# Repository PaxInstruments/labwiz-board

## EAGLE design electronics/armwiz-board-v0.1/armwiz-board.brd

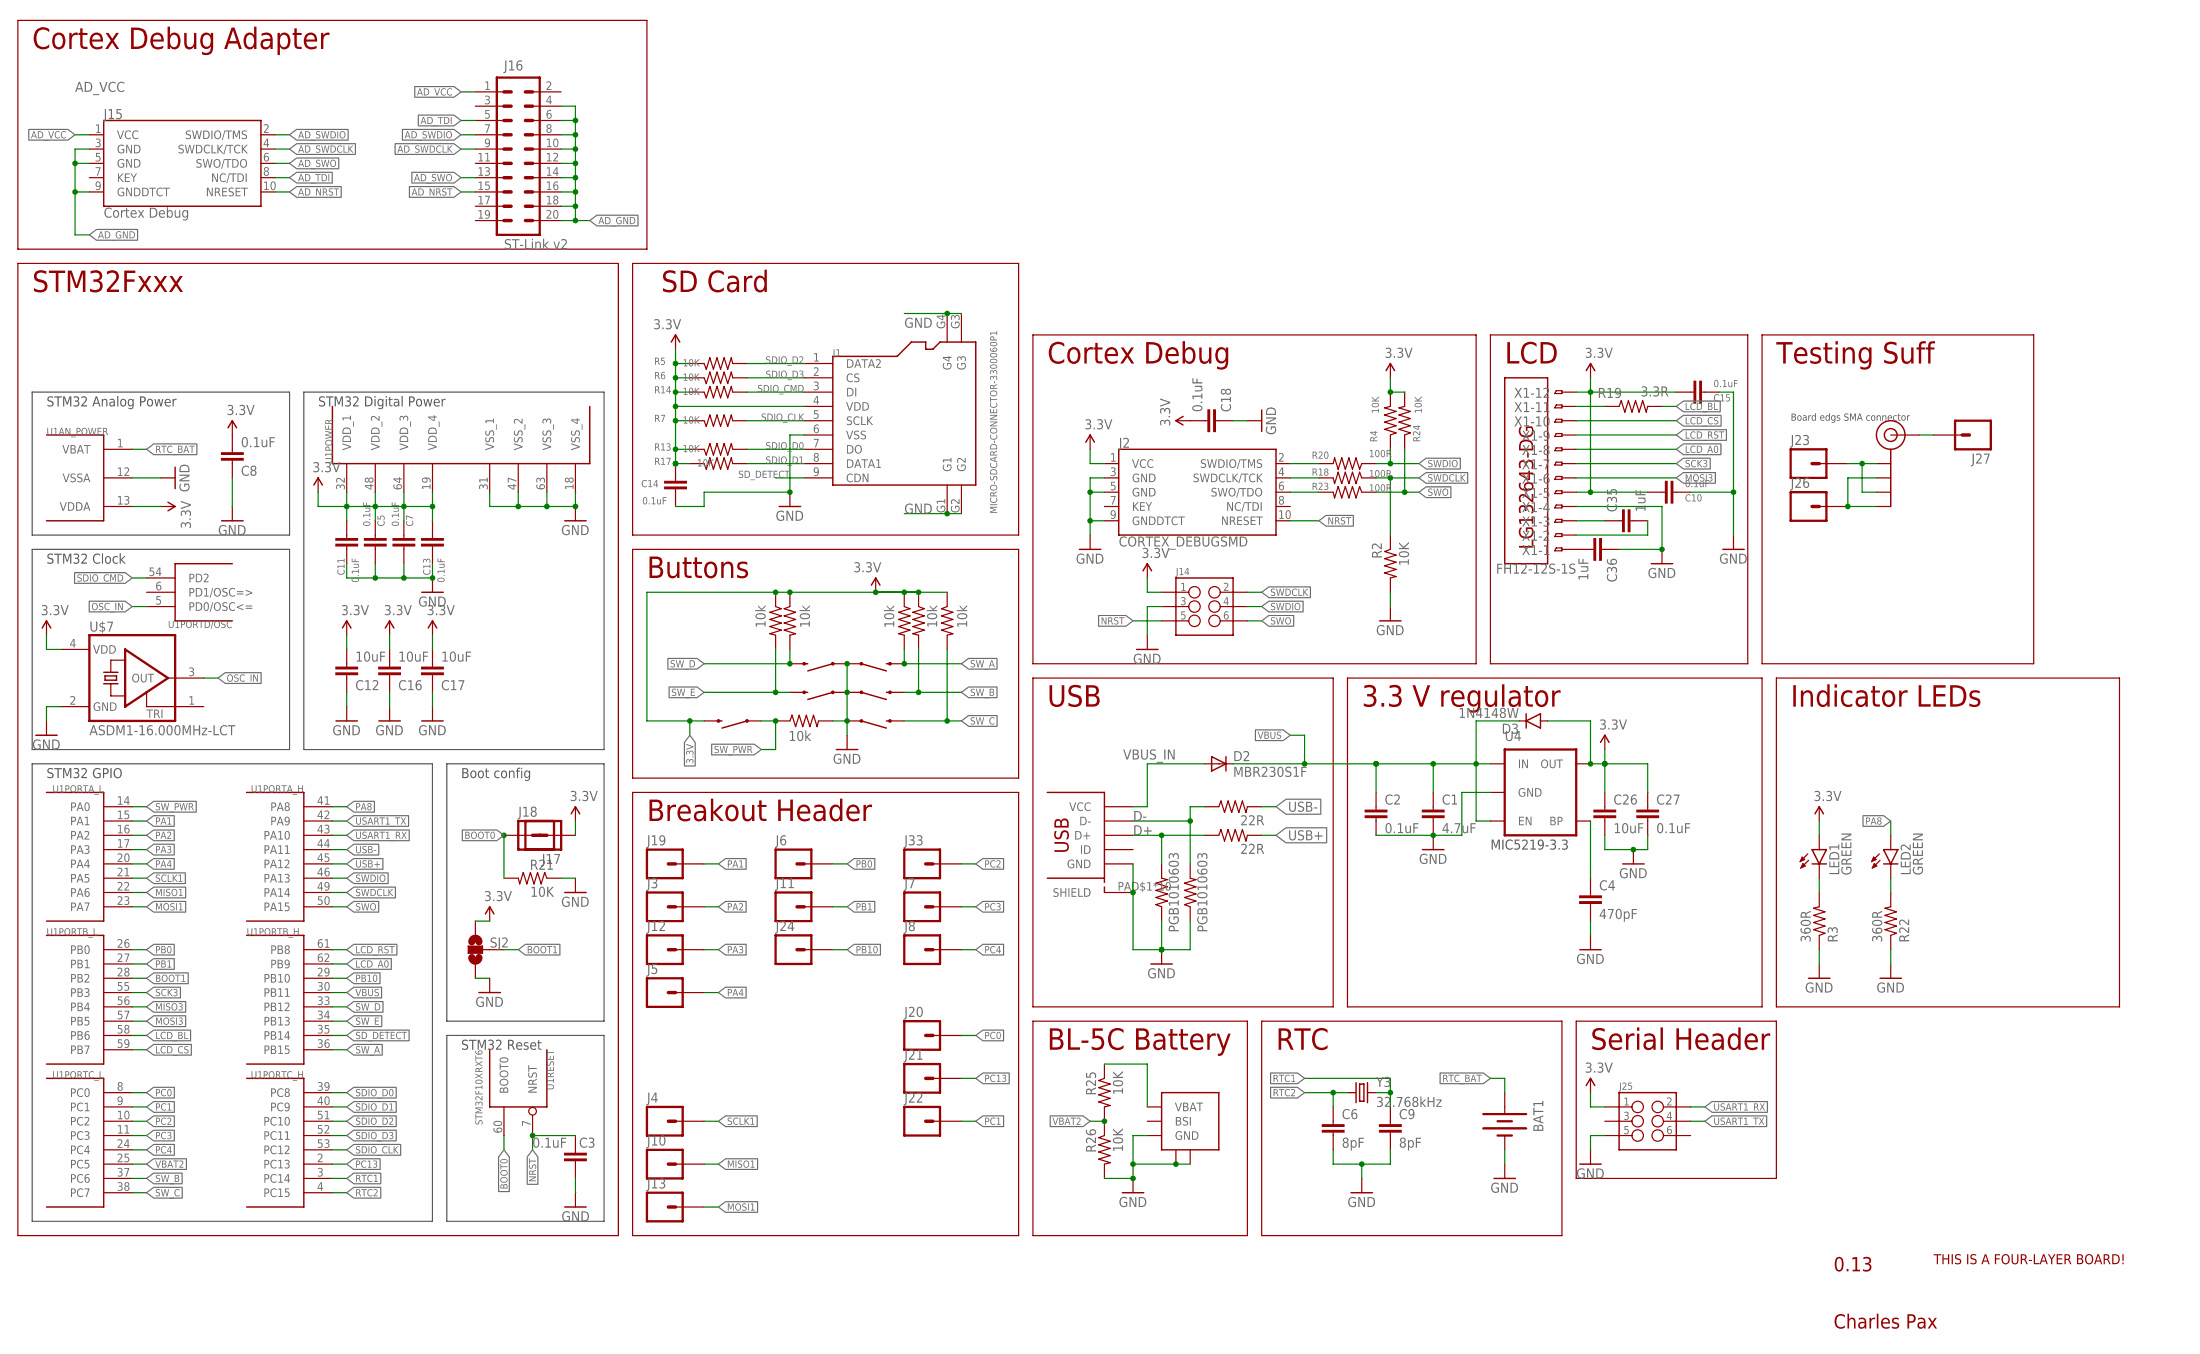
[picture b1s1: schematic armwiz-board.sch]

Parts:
BAT1: BATTERY12MM; BATTCON_12MM
C1: 4.7uF; C0402K
C2, C3, C5, C7, C8, C10, C11, C13, C14, C15, C18, C27: 0.1uF; C0402K
C4: 470pF; C0402K
C6, C9: 8pF; C0402K
C12, C16, C17, C26: 10uF; C0402K
C35, C36: 1uF; C0402K
D2: MBR230S1F; SOD123; MPN MBR230S1F-7
D3: 1N4148W; SOD-123
J1: MICRO-SDCARD-CONNECTOR-3300060P1; 9P-SMD-W-RING; MPN ST-TF-003A
J2: CORTEX_DEBUGSMD; SAMTECH_FTSH-105-01
J3, J4, J5, J6, J7, J8, J10, J11, J12, J13, J19, J20, J21, J22, J23, J24, J26, J27, J33: M01PTH; 1X01
J14, J25: M03X2PAX; CONNECTORS_2X3_SMT_POSTS_T400
J15: Cortex Debug; SAMTECH_FTSH-105-01
J16: ST-Link v2; 2X10
J17, J18: M01NOSILK-KIT; 1X01NS-KIT
J$1: SMA_EDGE; SMA-EDGE
LED1, LED2: GREEN; LED-0603
R1, R8, R11, R12, R15, R16: 10k; R0402
R2, R4, R5, R6, R7, R13, R14, R17, R21, R24, R25, R26: 10K; R0402
R3, R22: 360R; R0402
R9, R10: 22R; R0402
R18, R20, R23: 100R; R0402
R19: 3.3R; R0402
S1, S2, S3, S4, S5, S6: SWITCH-MOMENTARY-2SMD; TACTILE_SWITCH_SMD; MPN RS-187R05A2-DS MT RT
SJ2: SOLDERJUMPER_2WAYS; SJ_3
U1: STM32F10XRXT6; TQFP64
U4: MIC5219-3.3V; SOT23-5; MPN MIC5219-3.3YM5 TR
U$1: USB_MICROSMT+THRUHULE; USB_MICRO_THRUHOLE; MPN 10118194-0001LF
U$2: FOUR_LAYER_WARNING
U$3: BL-5C-CONNECTOR
U$5: LG132643-DG; MPN LG132643-DW
U$7: ASDM1-16.000MHz-LCT; ASE
X1: FH12-12S-1S; FH12-12S-1SH; MPN FH12-12S-1SH(55)
Y3: 32.768kHz; CRYSTAL-SMD-3.2X1.5MM
Z1, Z2: PGB1010603; SPARKFUN-RESISTORS_0603-RES; MPN PGB1010603NRHF

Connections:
3.3V: C5.1, C7.1, C8.2, C10.2, C11.2, C12.2, C13.2, C14.2, C15.2, C16.2, C17.2, C18.2, C26.1, C27.1, D3.A, J1.4 (VDD), J2.1 (VCC), J14.1, J18.1, J25.1, LED1.A, R4.2, R5.1, R6.1, R7.1, R8.1, R11.1, R12.1, R13.1, R14.1, R15.1, R16.1, R17.1, R24.2, S6.3 (2), SJ2.3, U1.13 (VDDA), U1.19 (VDD_4), U1.32 (VDD_1), U1.48 (VDD_2), U1.64 (VDD_3), U4.5 (OUT), U$7.4 (VDD), X1.5, X1.12
AD_GND: J15.3 (GND), J15.5 (GND), J15.9 (GNDDTCT), J16.4, J16.6, J16.8, J16.10, J16.12, J16.14, J16.16, J16.18, J16.20
AD_NRST: J15.10 (NRESET), J16.15
AD_SWDCLK: J15.4 (SWDCLK/TCK), J16.9
AD_SWDIO: J15.2 (SWDIO/TMS), J16.7
AD_SWO: J15.6 (SWO/TDO), J16.13
AD_TDI: J15.8 (NC/TDI), J16.5
AD_VCC: J15.1 (VCC), J16.1
BOOT0: J17.1, R21.2, U1.60 (BOOT0)
BOOT1: SJ2.2, U1.28 (PB2)
D+: R9.1, U$1.PIN$3 (D+), Z1.2
D-: R10.1, U$1.PIN$2 (D-), Z2.2
GND: BAT1.GND (-), C1.2, C2.2, C3.2, C4.2, C5.2, C6.2, C7.2, C8.1, C9.2, C10.1, C11.1, C12.1, C13.1, C14.1, C15.1, C16.1, C17.1, C18.1, C26.2, C27.2, C36.1, J1.6 (VSS), J1.G1, J1.G2, J1.G3, J1.G4, J2.3 (GND), J2.5 (GND), J2.9 (GNDDTCT), J14.3, J25.5, R1.2, R2.2, R3.1, R21.1, R22.1, R26.2, S1.1, S2.1, S3.1, S4.1, S5.1, SJ2.1, U1.12 (VSSA), U1.18 (VSS_4), U1.31 (VSS_1), U1.47 (VSS_2), U1.63 (VSS_3), U4.2 (GND), U$1.PAD$1 (SHIELD), U$1.PAD$2 (SHIELD), U$1.PAD$3 (SHIELD), U$1.PAD$4 (SHIELD), U$1.PAD$5 (SHIELD), U$1.PAD$6 (SHIELD), U$1.PAD$7 (SHIELD), U$1.PAD$8 (SHIELD), U$1.PAD$9 (SHIELD), U$1.PAD$10 (SHIELD), U$1.PIN$5 (GND), U$3.P$3 (GND), U$3.P$4, U$3.P$5, U$7.2 (GND), X1.4, Z1.1, Z2.1
LCD_A0: U1.62 (PB9), X1.8
LCD_BL: R19.2, U1.58 (PB6)
LCD_CS: U1.59 (PB7), X1.10
LCD_RST: U1.61 (PB8), X1.9
MISO1: J10.1, U1.22 (PA6)
MISO3: U1.56 (PB4)
MOSI1: J13.1, U1.23 (PA7)
MOSI3: U1.57 (PB5), X1.6
unnamed: C4.1, U4.4 (BP)
unnamed: R19.1, X1.11
unnamed: J2.4 (SWDCLK/TCK), R18.2
unnamed: LED1.C, R3.2
unnamed: LED2.C, R22.2
unnamed: J2.6 (SWO/TDO), R23.2
unnamed: J2.2 (SWDIO/TMS), R20.2
unnamed: J26.1, J$1.GND@1 (GND), J$1.GND@3 (GND)
unnamed: J23.1, J$1.GND@0 (GND), J$1.GND@2 (GND)
unnamed: R25.1, U$3.P$1 (VBAT)
unnamed: J27.1, J$1.SIG (SIGNAL)
unnamed: C35.1, X1.3
unnamed: C35.2, X1.2
unnamed: C36.2, X1.1
NRST: C3.1, J2.10 (NRESET), J14.5, U1.7 (NRST)
OSC_IN: U1.5 (PD0/OSC<=), U$7.3 (OUT)
PA1: J19.1, U1.15 (PA1)
PA2: J3.1, U1.16 (PA2)
PA3: J12.1, U1.17 (PA3)
PA4: J5.1, U1.20 (PA4)
PA8: LED2.A, U1.41 (PA8)
PB0: J6.1, U1.26 (PB0)
PB1: J11.1, U1.27 (PB1)
PB10: J24.1, U1.29 (PB10)
PC0: J20.1, U1.8 (PC0)
PC1: J22.1, U1.9 (PC1)
PC2: J33.1, U1.10 (PC2)
PC3: J7.1, U1.11 (PC3)
PC4: J8.1, U1.24 (PC4)
PC13: J21.1, U1.2 (PC13)
RTC1: C9.1, U1.3 (PC14), Y3.P$2 (2)
RTC2: C6.1, U1.4 (PC15), Y3.P$1 (1)
RTC_BAT: BAT1.PWR@1 (+), U1.1 (VBAT)
SCK3: U1.55 (PB3), X1.7
SCLK1: J4.1, U1.21 (PA5)
SDIO_CLK: J1.5 (SCLK), R7.2, U1.53 (PC12)
SDIO_CMD: J1.3 (DI), R14.2, U1.54 (PD2)
SDIO_D0: J1.7 (DO), R13.2, U1.39 (PC8)
SDIO_D1: J1.8 (DATA1), R17.2, U1.40 (PC9)
SDIO_D2: J1.1 (DATA2), R5.2, U1.51 (PC10)
SDIO_D3: J1.2 (CS), R6.2, U1.52 (PC11)
SD_DETECT: J1.9 (CDN), U1.35 (PB14)
SWDCLK: J14.2, R2.1, R18.1, U1.49 (PA14)
SWDIO: J14.4, R4.1, R20.1, U1.46 (PA13)
SWO: J14.6, R23.1, R24.1, U1.50 (PA15)
SW_A: R8.2, S3.3 (2), U1.36 (PB15)
SW_B: R11.2, S2.3 (2), U1.37 (PC6)
SW_C: R12.2, S1.3 (2), U1.38 (PC7)
SW_D: R15.2, S4.3 (2), U1.33 (PB12)
SW_E: R16.2, S5.3 (2), U1.34 (PB13)
SW_PWR: R1.1, S6.1, U1.14 (PA0)
USART1_RX: J25.2, U1.43 (PA10)
USART1_TX: J25.4, U1.42 (PA9)
USB+: R9.2, U1.45 (PA12)
USB-: R10.2, U1.44 (PA11)
VBAT2: R25.2, R26.1, U1.25 (PC5)
VBUS: C1.1, C2.1, D2.C, D3.C, U1.30 (PB11), U4.1 (IN), U4.3 (EN)
VBUS_IN: D2.A, U$1.PIN$1 (VCC)

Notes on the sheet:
MIC5219-3.3
USB
3.3 V regulator
LCD
Buttons
0.13
Charles Pax
SD Card
STM32 Digital Power
STM32 Analog Power
STM32 Clock
STM32 Reset
STM32Fxxx
STM32 GPIO
Serial Header
RTC
Breakout Header
BL-5C Battery
Boot config
Cortex Debug
Cortex Debug Adapter
Indicator LEDs
Testing Suff
Board edgs SMA connector

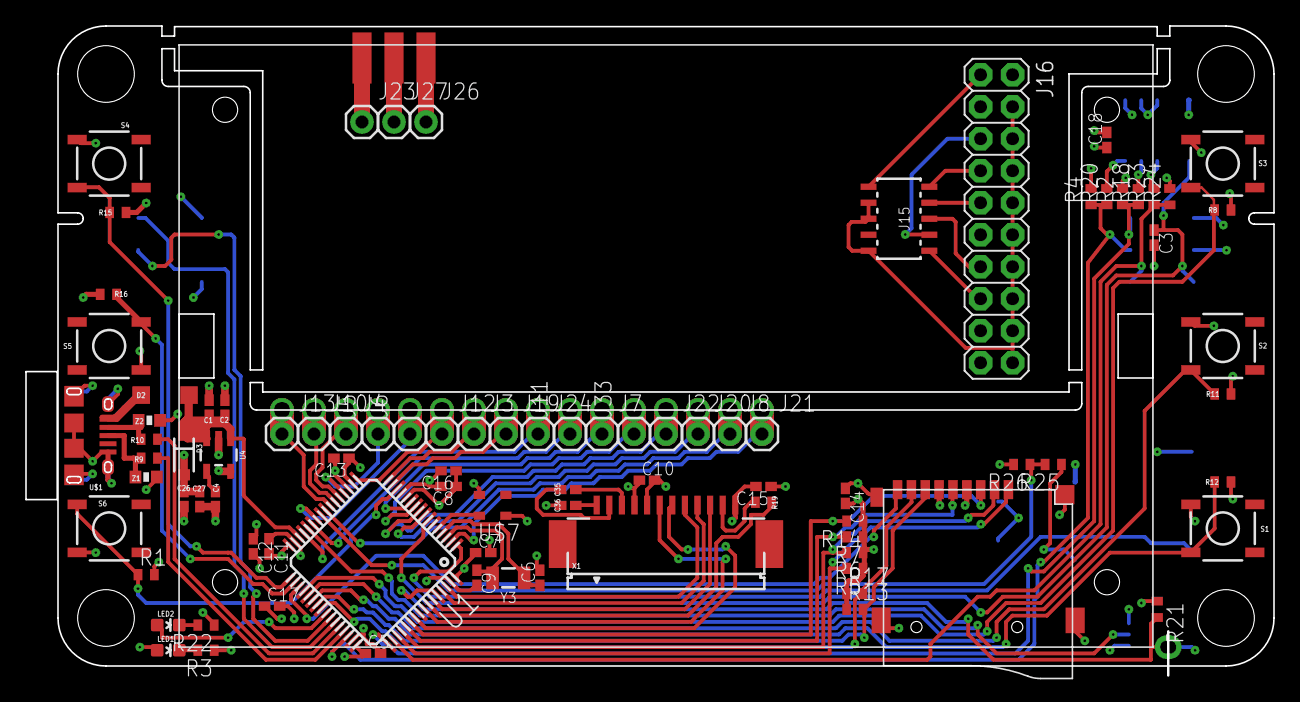
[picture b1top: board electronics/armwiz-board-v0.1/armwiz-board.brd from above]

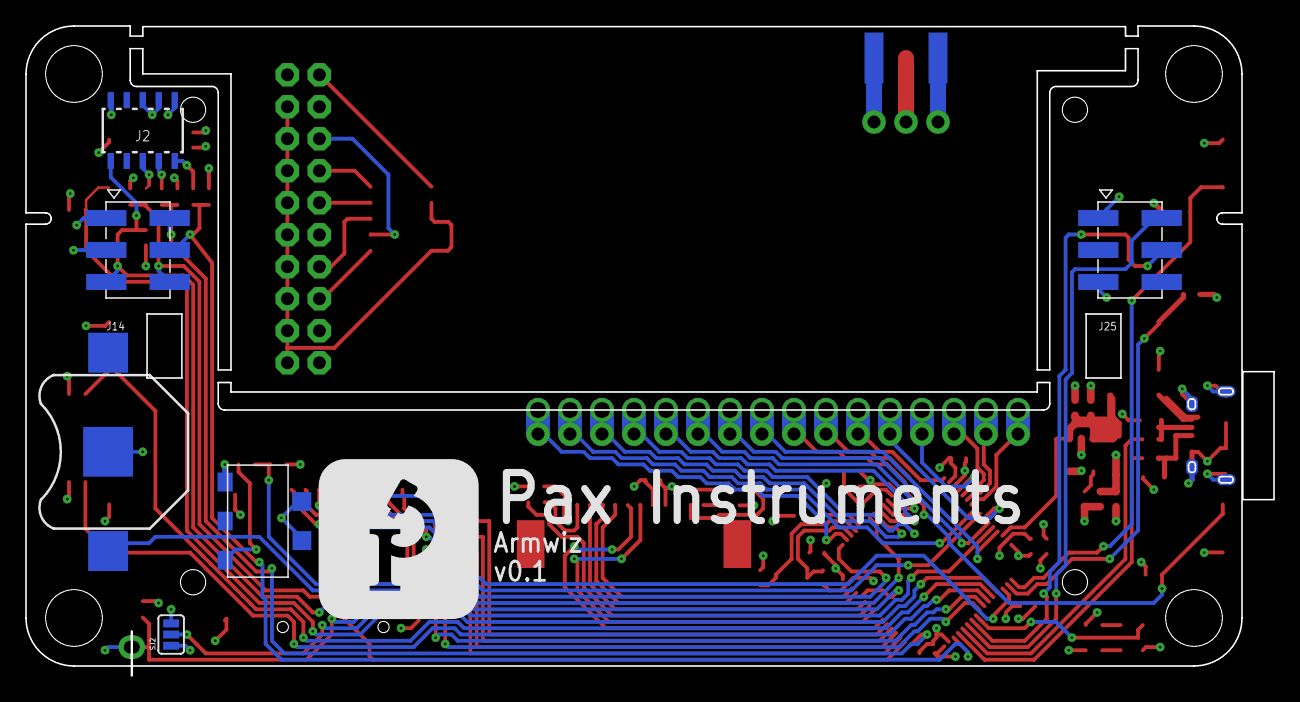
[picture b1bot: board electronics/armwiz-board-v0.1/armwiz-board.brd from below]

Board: 4 copper layers, 99.1 x 51.5 mm, 100 parts (8 on the bottom side), 78 nets.

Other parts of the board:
U$6: PAX-LOGO-0.5IN

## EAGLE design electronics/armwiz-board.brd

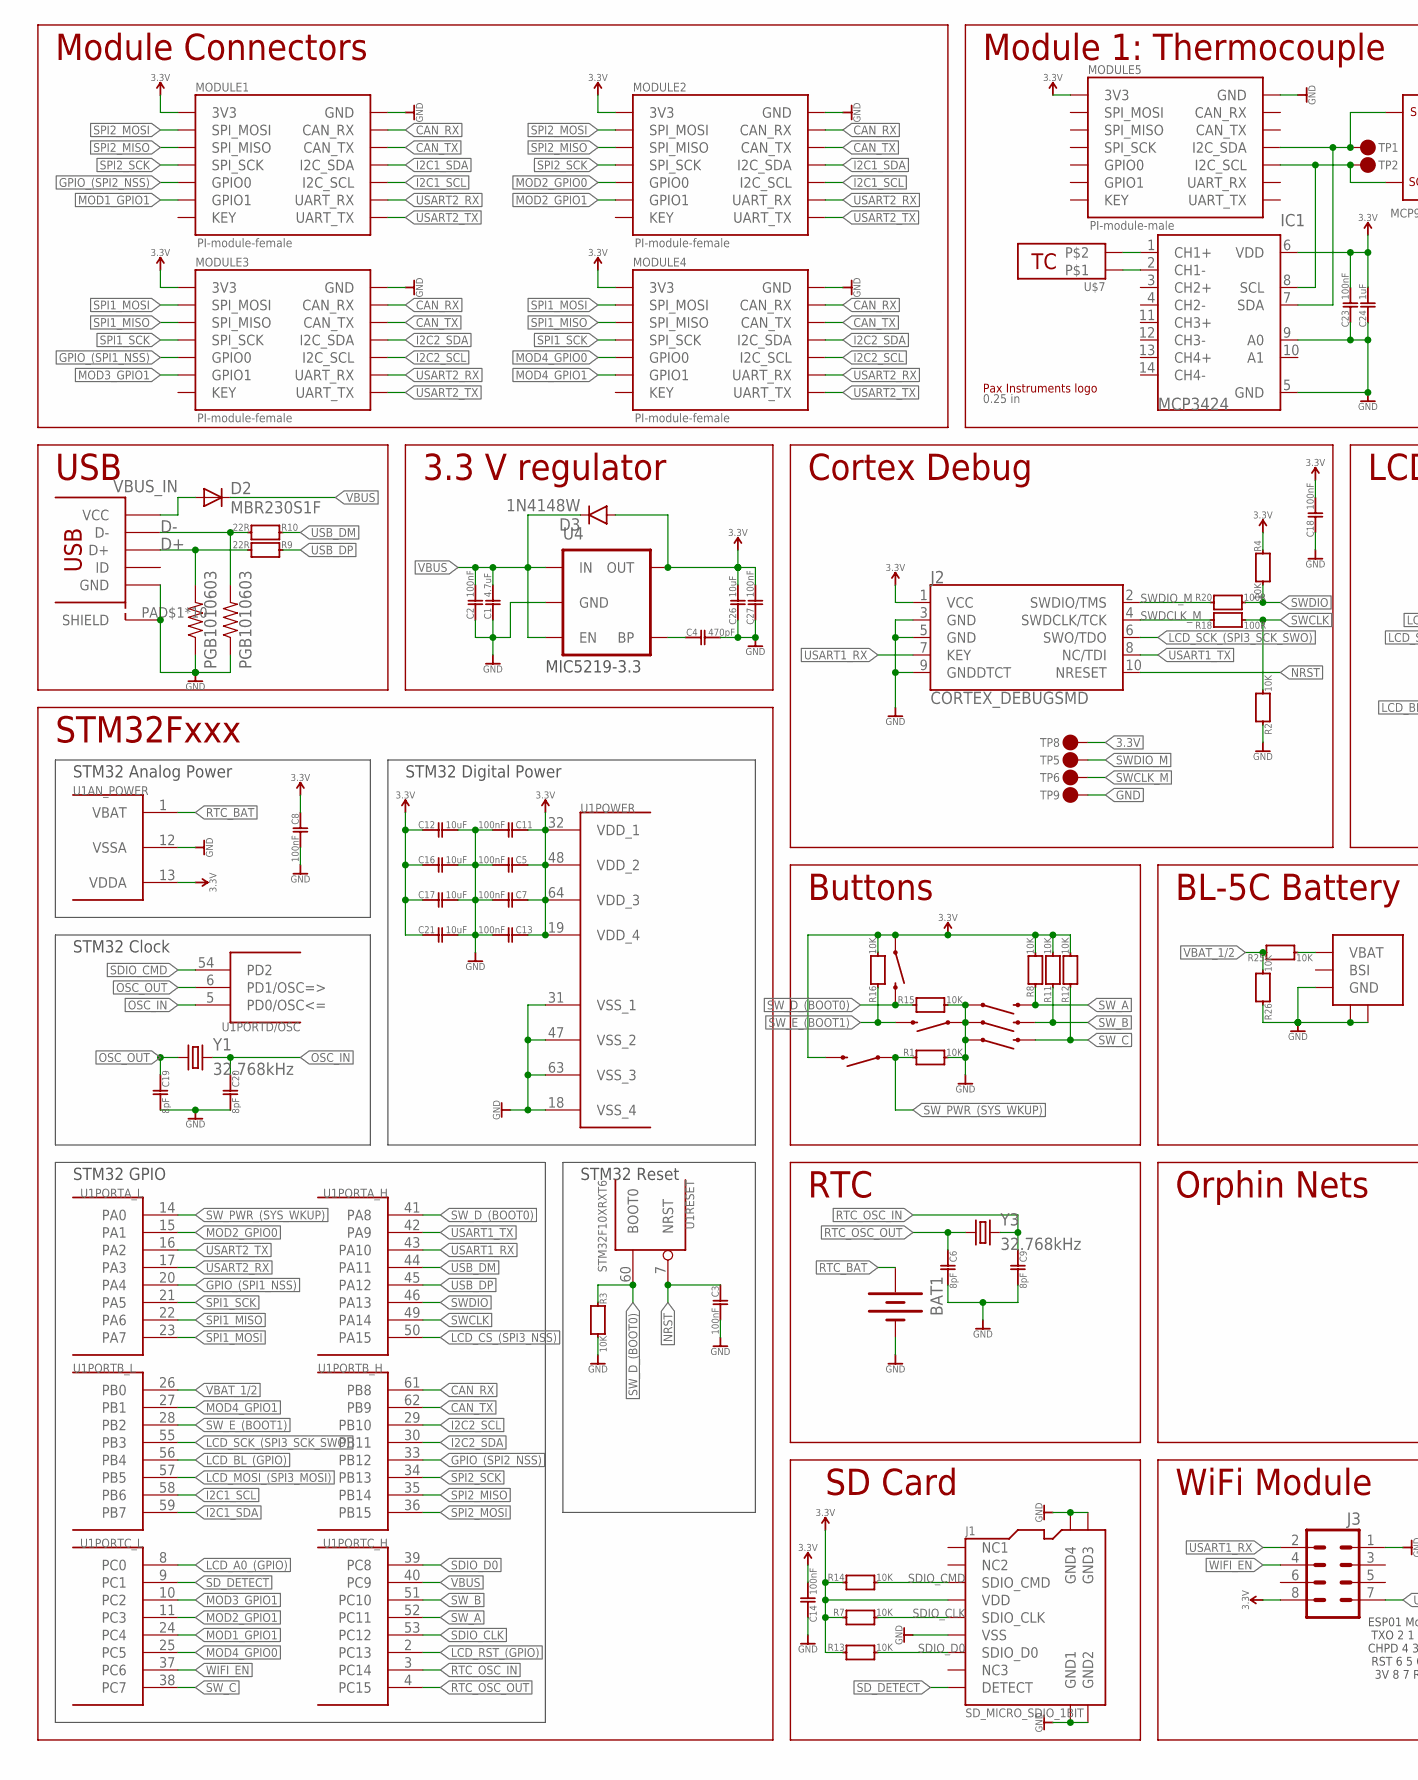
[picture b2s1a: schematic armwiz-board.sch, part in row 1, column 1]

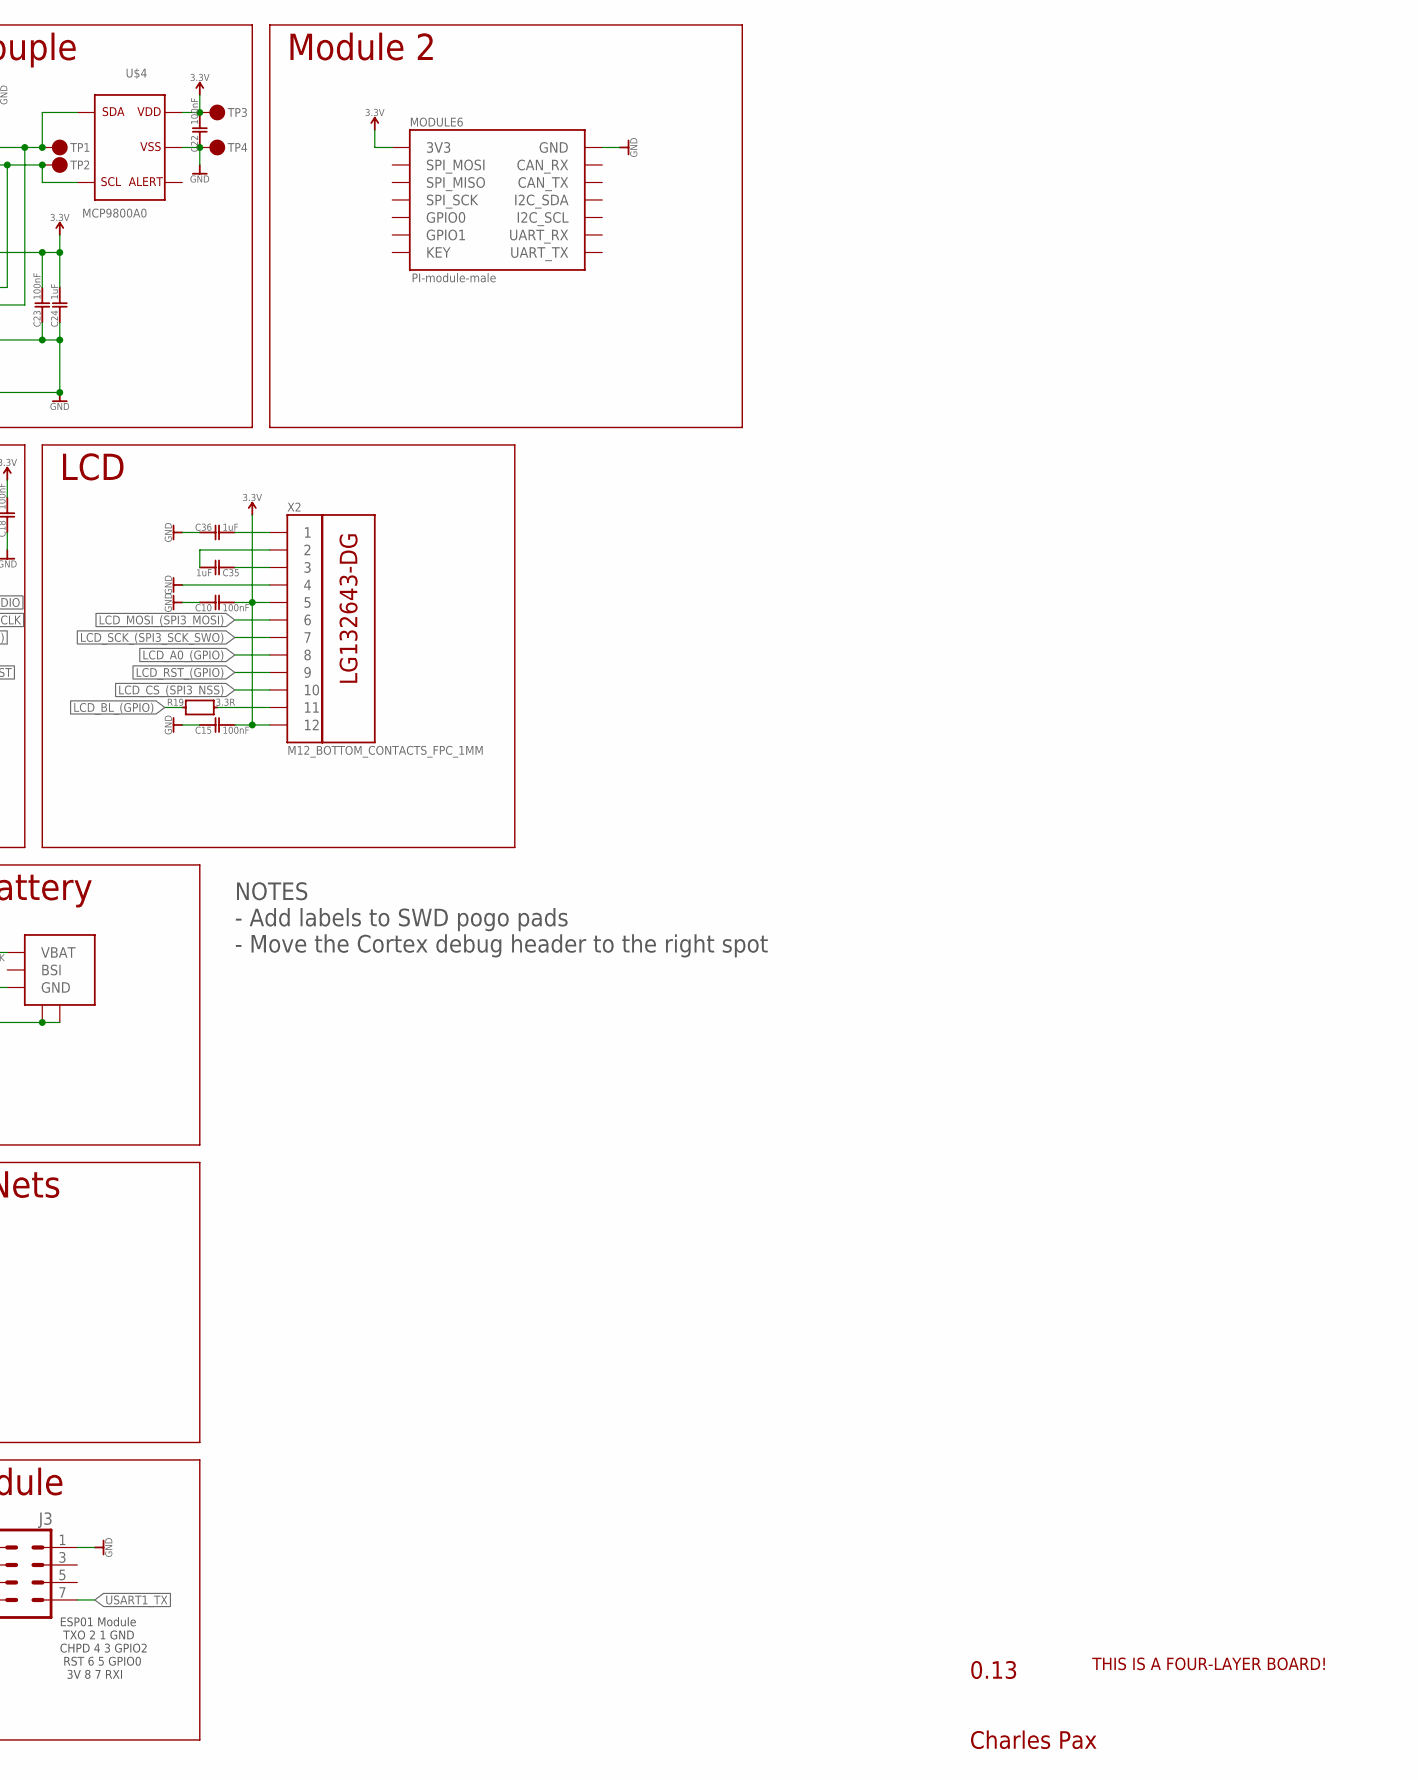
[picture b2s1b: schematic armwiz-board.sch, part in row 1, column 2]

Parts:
BAT1: BATTERY12MM; BATTCON_12MM
C1: 4.7uF; 0402
C2, C3, C5, C7, C8, C10, C11, C13, C14, C15, C18, C22, C23, C27: 100nF; 0402
C4: 470pF; 0402
C6, C9, C19, C20: 8pF; 0402
C12, C16, C17, C21, C26: 10uF; 0402
C24, C35, C36: 1uF; 0402
D2: MBR230S1F; SOD123; MPN MBR230S1F-7
D3: 1N4148W; SOD-123
IC1: MCP3424; SO14
J1: SD_MICRO_SDIO_1BIT; SD_MICRO_1
J2: CORTEX_DEBUGSMD; SAMTECH_FTSH-105-01
J3: M04X2; 2X4
MODULE1, MODULE2, MODULE3, MODULE4: PI-module-female; M07X2_2MM_EDGE
MODULE5, MODULE6: PI-module-male; M07X2_2MM_EDGE
R1, R2, R3, R4, R7, R8, R11, R12, R13, R14, R15, R16, R25, R26: 10K; 0402
R9, R10: 22R; R0402
R18, R20: 100R; 0402
R19: 3.3R; 0402
S1, S2, S3, S4, S5, S6: SWITCH-MOMENTARY-2SMD; TACTILE_SWITCH_SMD; MPN RS-187R05A2-DS MT RT
TP1, TP2, TP3, TP4: M01_TH
TP5, TP6, TP8, TP9: M01_PAD_1MM; PAD_1MM
U1: STM32F10XRXT6; TQFP64
U4: MIC5219-3.3V; SOT23-5; MPN MIC5219-3.3YM5 TR
U$1: USB_MICROSMT+THRUHULE; USB_MICRO_THRUHOLE; MPN 10118194-0001LF
U$2: FOUR_LAYER_WARNING
U$3: BL-5C-CONNECTOR
U$4: MCP9800A0; SOT23-5L
U$5: LG132643-DG; MPN LG132643-DW
U$7: THERMOCOUPLE_MINI_INSIDE; THERMOCOUPLE_CLIP_INSIDE
U$8: 0.25 in; PAX-LOGO-0.25IN
X2: M12_BOTTOM_CONTACTS_FPC_1MM; FPC_12P_1MM
Y1, Y3: 32.768kHz; CRYSTAL-SMD-3.2X1.5MM
Z1, Z2: PGB1010603; SPARKFUN-RESISTORS_0603-RES; MPN PGB1010603NRHF

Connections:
3.3V: C5.1, C7.1, C8.1, C10.2, C11.1, C12.1, C13.1, C14.2, C15.2, C16.1, C17.1, C18.2, C21.1, C26.2, C27.2, D3.A, J1.4 (VDD), J2.1 (VCC), J3.8, MODULE1.P$1 (3V3), MODULE2.P$1 (3V3), MODULE3.P$1 (3V3), MODULE4.P$1 (3V3), R4.2, R7.2, R8.1, R11.1, R12.1, R13.2, R14.2, R16.1, S4.1, S6.3 (2), TP8.P$1, U1.13 (VDDA), U1.19 (VDD_4), U1.32 (VDD_1), U1.48 (VDD_2), U1.64 (VDD_3), U4.5 (OUT), X2.5, X2.12
3.3V_1: C22.2, C23.2, C24.2, IC1.6 (VDD), MODULE5.P$13 (3V3), TP3.P$1, U$4.1
3.3V_2: MODULE6.P$13 (3V3)
CAN_RX: MODULE1.P$4 (CAN_RX), MODULE2.P$4 (CAN_RX), MODULE3.P$4 (CAN_RX), MODULE4.P$4 (CAN_RX), U1.61 (PB8)
CAN_TX: MODULE1.P$6 (CAN_TX), MODULE2.P$6 (CAN_TX), MODULE3.P$6 (CAN_TX), MODULE4.P$6 (CAN_TX), U1.62 (PB9)
D+: R9.1, U$1.PIN$3 (D+), Z1.2
D-: R10.1, U$1.PIN$2 (D-), Z2.2
GND: BAT1.GND (-), C1.1, C2.1, C3.2, C4.2, C5.2, C6.2, C7.2, C8.2, C9.2, C10.1, C11.2, C12.2, C13.2, C14.1, C15.1, C16.2, C17.2, C18.1, C19.2, C20.2, C21.2, C26.1, C27.1, C36.1, J1.6 (VSS), J1.G1 (GND1), J1.G2 (GND2), J1.G3 (GND3), J1.G4 (GND4), J2.3 (GND), J2.5 (GND), J2.9 (GNDDTCT), J3.1, MODULE1.P$2 (GND), MODULE2.P$2 (GND), MODULE3.P$2 (GND), MODULE4.P$2 (GND), R1.1, R2.2, R3.1, R15.1, R26.2, S1.1, S2.1, S3.1, S5.1, TP9.P$1, U1.12 (VSSA), U1.18 (VSS_4), U1.31 (VSS_1), U1.47 (VSS_2), U1.63 (VSS_3), U4.2 (GND), U$1.PAD$1 (SHIELD), U$1.PAD$2 (SHIELD), U$1.PAD$3 (SHIELD), U$1.PAD$4 (SHIELD), U$1.PAD$5 (SHIELD), U$1.PAD$6 (SHIELD), U$1.PAD$7 (SHIELD), U$1.PAD$8 (SHIELD), U$1.PAD$9 (SHIELD), U$1.PAD$10 (SHIELD), U$1.PIN$5 (GND), U$3.P$3 (GND), U$3.P$4, U$3.P$5, X2.4, Z1.1, Z2.1
GND_1: C22.1, C23.1, C24.1, IC1.5 (GND), IC1.9 (A0), MODULE5.P$14 (GND), TP4.P$1, U$4.2
GND_2: MODULE6.P$14 (GND)
GPIO_(SPI1_NSS): MODULE3.P$9 (GPIO0), U1.20 (PA4)
GPIO_(SPI2_NSS): MODULE1.P$9 (GPIO0), U1.33 (PB12)
I2C1_SCL: MODULE1.P$10 (I2C_SCL), MODULE2.P$10 (I2C_SCL), U1.58 (PB6)
I2C1_SDA: MODULE1.P$8 (I2C_SDA), MODULE2.P$8 (I2C_SDA), U1.59 (PB7)
I2C2_SCL: MODULE3.P$10 (I2C_SCL), MODULE4.P$10 (I2C_SCL), U1.29 (PB10)
I2C2_SDA: MODULE3.P$8 (I2C_SDA), MODULE4.P$8 (I2C_SDA), U1.30 (PB11)
LCD_A0_(GPIO): U1.8 (PC0), X2.8
LCD_BL_(GPIO): R19.2, U1.56 (PB4)
LCD_CS_(SPI3_NSS): U1.50 (PA15), X2.10
LCD_MOSI_(SPI3_MOSI): U1.57 (PB5), X2.6
LCD_RST_(GPIO): U1.2 (PC13), X2.9
LCD_SCK_(SPI3_SCK_SWO): J2.6 (SWO/TDO), U1.55 (PB3), X2.7
MOD1_GPIO1: MODULE1.P$11 (GPIO1), U1.24 (PC4)
MOD2_GPIO0: MODULE2.P$9 (GPIO0), U1.15 (PA1)
MOD2_GPIO1: MODULE2.P$11 (GPIO1), U1.11 (PC3)
MOD3_GPIO1: MODULE3.P$11 (GPIO1), U1.10 (PC2)
MOD4_GPIO0: MODULE4.P$9 (GPIO0), U1.25 (PC5)
MOD4_GPIO1: MODULE4.P$11 (GPIO1), U1.27 (PB1)
unnamed: C4.1, U4.4 (BP)
unnamed: R19.1, X2.11
unnamed: R25.1, U$3.P$1 (VBAT)
unnamed: IC1.2 (CH1-), U$7.P$1
unnamed: IC1.1 (CH1+), U$7.P$2
unnamed: C35.1, X2.3
unnamed: C35.2, X2.2
unnamed: C36.2, X2.1
NRST: C3.1, J2.10 (NRESET), U1.7 (NRST)
OSC_IN: C20.1, U1.5 (PD0/OSC<=), Y1.P$2 (2)
OSC_OUT: C19.1, U1.6 (PD1/OSC=>), Y1.P$1 (1)
RTC_BAT: BAT1.PWR@1 (+), U1.1 (VBAT)
RTC_OSC_IN: C9.1, U1.3 (PC14), Y3.P$2 (2)
RTC_OSC_OUT: C6.1, U1.4 (PC15), Y3.P$1 (1)
SCL_1: IC1.8 (SCL), MODULE5.P$6 (I2C_SCL), TP2.P$1, U$4.4
SDA_1: IC1.7 (SDA), MODULE5.P$8 (I2C_SDA), TP1.P$1, U$4.5
SDIO_CLK: J1.5 (SDIO_CLK), R7.1, U1.53 (PC12)
SDIO_CMD: J1.3 (SDIO_CMD), R14.1, U1.54 (PD2)
SDIO_D0: J1.7 (SDIO_D0), R13.1, U1.39 (PC8)
SD_DETECT: J1.9 (DETECT), U1.9 (PC1)
SPI1_MISO: MODULE3.P$5 (SPI_MISO), MODULE4.P$5 (SPI_MISO), U1.22 (PA6)
SPI1_MOSI: MODULE3.P$3 (SPI_MOSI), MODULE4.P$3 (SPI_MOSI), U1.23 (PA7)
SPI1_SCK: MODULE3.P$7 (SPI_SCK), MODULE4.P$7 (SPI_SCK), U1.21 (PA5)
SPI2_MISO: MODULE1.P$5 (SPI_MISO), MODULE2.P$5 (SPI_MISO), U1.35 (PB14)
SPI2_MOSI: MODULE1.P$3 (SPI_MOSI), MODULE2.P$3 (SPI_MOSI), U1.36 (PB15)
SPI2_SCK: MODULE1.P$7 (SPI_SCK), MODULE2.P$7 (SPI_SCK), U1.34 (PB13)
SWCLK: R2.1, R18.1, U1.49 (PA14)
SWCLK_M: TP6.P$1
SWDCLK_M: J2.4 (SWDCLK/TCK), R18.2
SWDIO: R4.1, R20.1, U1.46 (PA13)
SWDIO_M: J2.2 (SWDIO/TMS), R20.2, TP5.P$1
SW_A: R8.2, S3.3 (2), U1.52 (PC11)
SW_B: R11.2, S2.3 (2), U1.51 (PC10)
SW_C: R12.2, S1.3 (2), U1.38 (PC7)
SW_D_(BOOT0): R3.2, R15.2, S4.3 (2), U1.41 (PA8), U1.60 (BOOT0)
SW_E_(BOOT1): R16.2, S5.3 (2), U1.28 (PB2)
SW_PWR_(SYS_WKUP): R1.2, S6.1, U1.14 (PA0)
USART1_RX: J2.7 (KEY), J3.2, U1.43 (PA10)
USART1_TX: J2.8 (NC/TDI), J3.7, U1.42 (PA9)
USART2_RX: MODULE1.P$12 (UART_RX), MODULE2.P$12 (UART_RX), MODULE3.P$12 (UART_RX), MODULE4.P$12 (UART_RX), U1.17 (PA3)
USART2_TX: MODULE1.P$14 (UART_TX), MODULE2.P$14 (UART_TX), MODULE3.P$14 (UART_TX), MODULE4.P$14 (UART_TX), U1.16 (PA2)
USB_DM: R10.2, U1.44 (PA11)
USB_DP: R9.2, U1.45 (PA12)
VBAT_1/2: R25.2, R26.1, U1.26 (PB0)
VBUS: C1.2, C2.2, D2.C, D3.C, U1.40 (PC9), U4.1 (IN), U4.3 (EN)
VBUS_IN: D2.A, U$1.PIN$1 (VCC)
WIFI_EN: J3.4, U1.37 (PC6)

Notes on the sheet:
MIC5219-3.3
USB
3.3 V regulator
LCD
Buttons
0.13
Charles Pax
SD Card
STM32 Digital Power
STM32 Analog Power
STM32 Clock
STM32 Reset
STM32Fxxx
STM32 GPIO
RTC
Module Connectors
BL-5C Battery
Cortex Debug
Orphin Nets
Module 1: Thermocouple
Module 2
NOTES - Add labels to SWD pogo pads - Move the Cortex debug header to the right spot
ESP01 Module TXO 2 1 GND CHPD 4 3 GPIO2 RST 6 5 GPIO0 3V 8 7 RXI
WiFi Module

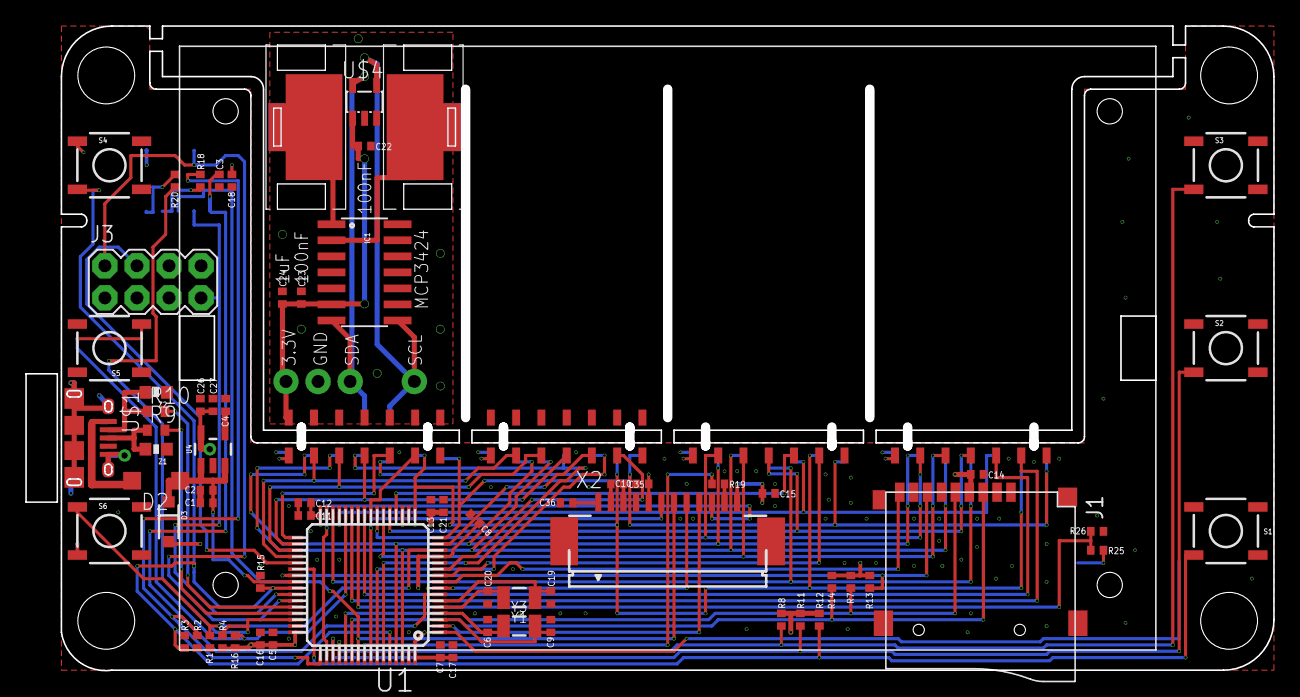
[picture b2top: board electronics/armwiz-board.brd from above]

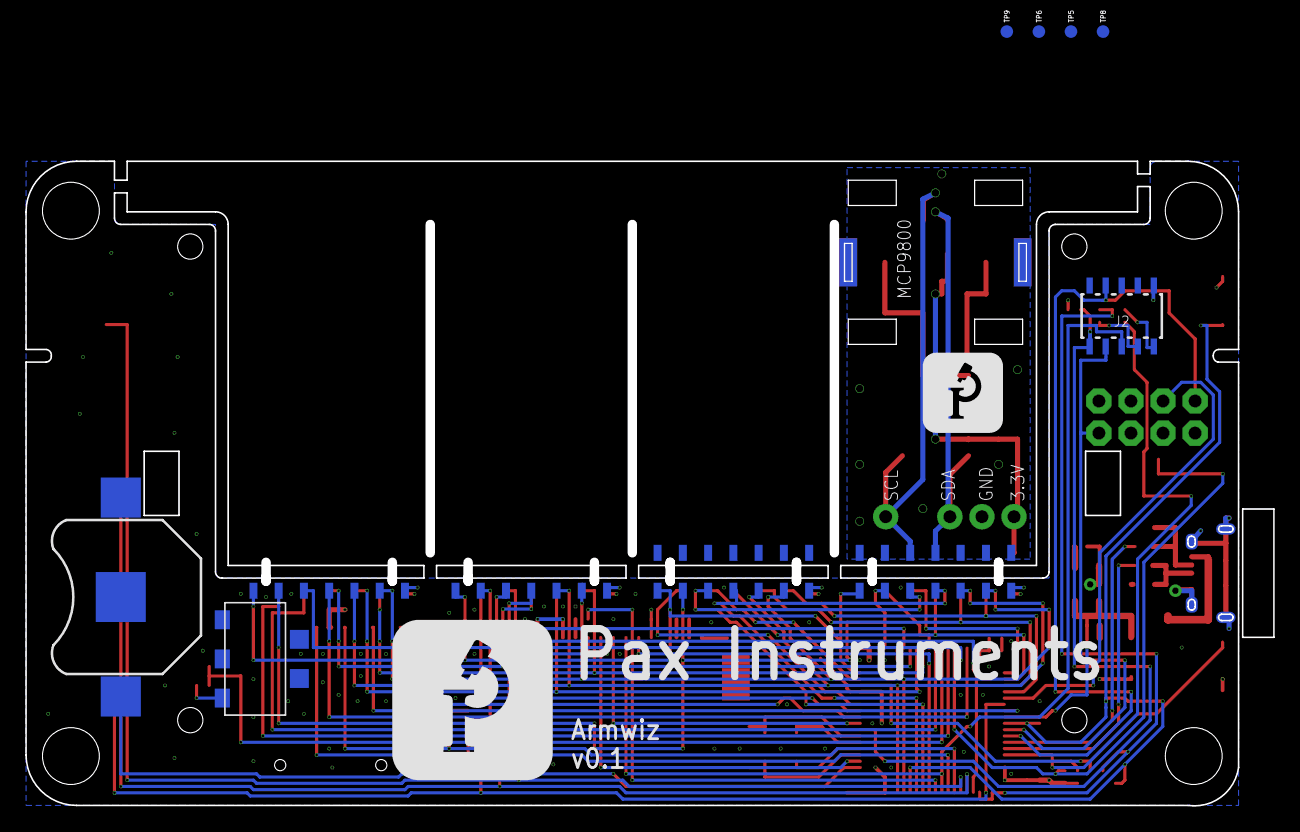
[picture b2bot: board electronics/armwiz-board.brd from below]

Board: 4 copper layers, 98.8 x 51.0 mm, 89 parts (10 on the bottom side), 72 nets.

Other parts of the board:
U$6: PAX-LOGO-0.5IN

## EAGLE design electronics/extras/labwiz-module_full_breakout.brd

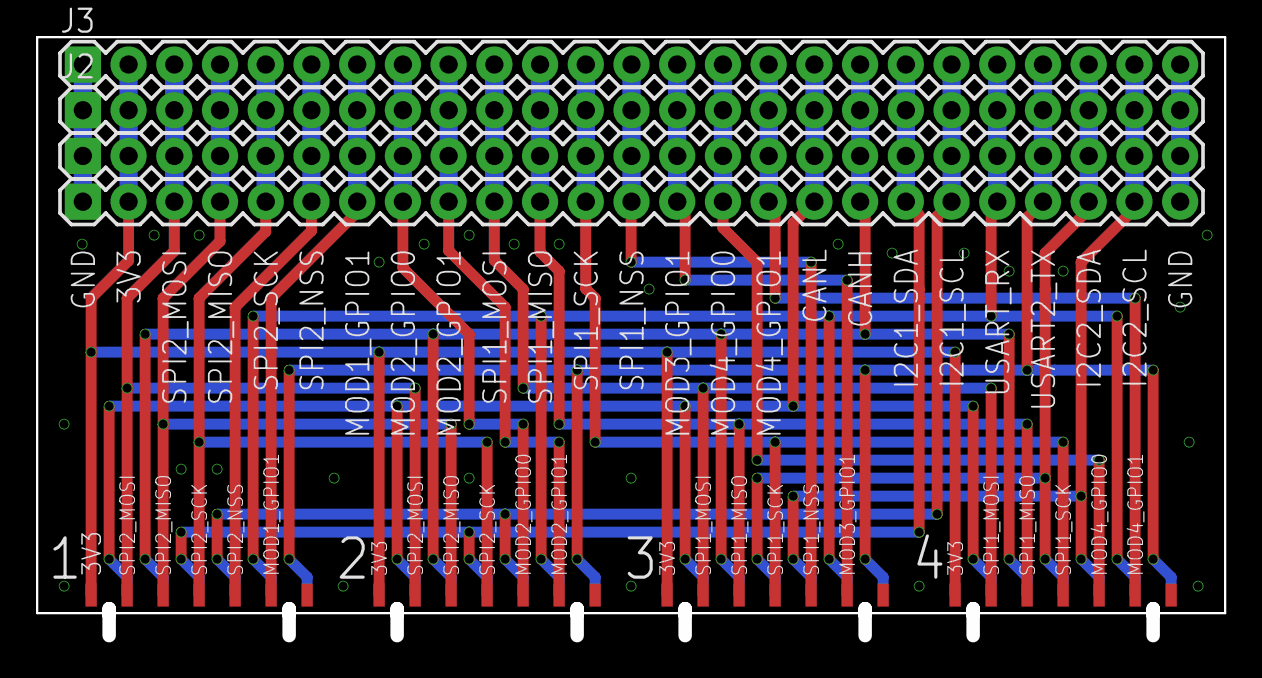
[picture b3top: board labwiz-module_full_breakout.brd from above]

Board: 4 copper layers, 66.0 x 33.2 mm, 8 parts (0 on the bottom side), 24 nets.

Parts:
J1, J2, J3, J4: 1X25
MODULE5, MODULE6, MODULE7, MODULE8: PI-module-male; M07X2_2MM_EDGE

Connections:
3.3V: J1.2, J2.2, J3.2, J4.2, MODULE5.P$13, MODULE6.P$13, MODULE7.P$13, MODULE8.P$13
CANH: J1.18, J2.18, J3.18, J4.18, MODULE5.P$10, MODULE6.P$10, MODULE7.P$10, MODULE8.P$10
CANL: J1.17, J2.17, J3.17, J4.17, MODULE5.P$12, MODULE6.P$12, MODULE7.P$12, MODULE8.P$12
GND: J1.1, J1.25, J2.1, J2.25, J3.1, J3.25, J4.1, J4.25, MODULE5.P$14, MODULE6.P$14, MODULE7.P$14, MODULE8.P$14
I2C1_SCL: J1.20, J2.20, J3.20, J4.20, MODULE5.P$6, MODULE6.P$6
I2C1_SDA: J1.19, J2.19, J3.19, J4.19, MODULE5.P$8, MODULE6.P$8
I2C2_SCL: J1.24, J2.24, J3.24, J4.24, MODULE7.P$6, MODULE8.P$6
I2C2_SDA: J1.23, J2.23, J3.23, J4.23, MODULE7.P$8, MODULE8.P$8
MOD1_GPIO1: J1.7, J2.7, J3.7, J4.7, MODULE5.P$3
MOD2_GPIO0: J1.8, J2.8, J3.8, J4.8, MODULE6.P$5
MOD2_GPIO1: J1.9, J2.9, J3.9, J4.9, MODULE6.P$3
MOD3_GPIO1: J1.14, J2.14, J3.14, J4.14, MODULE7.P$3
MOD4_GPIO0: J1.15, J2.15, J3.15, J4.15, MODULE8.P$5
MOD4_GPIO1: J1.16, J2.16, J3.16, J4.16, MODULE8.P$3
SPI1_MISO: J1.11, J2.11, J3.11, J4.11, MODULE7.P$9, MODULE8.P$9
SPI1_MOSI: J1.10, J2.10, J3.10, J4.10, MODULE7.P$11, MODULE8.P$11
SPI1_NSS: J1.13, J2.13, J3.13, J4.13, MODULE7.P$5
SPI1_SCK: J1.12, J2.12, J3.12, J4.12, MODULE7.P$7, MODULE8.P$7
SPI2_MISO: J1.4, J2.4, J3.4, J4.4, MODULE5.P$9, MODULE6.P$9
SPI2_MOSI: J1.3, J2.3, J3.3, J4.3, MODULE5.P$11, MODULE6.P$11
SPI2_NSS: J1.6, J2.6, J3.6, J4.6, MODULE5.P$5
SPI2_SCK: J1.5, J2.5, J3.5, J4.5, MODULE5.P$7, MODULE6.P$7
USART2_RX: J1.21, J2.21, J3.21, J4.21, MODULE5.P$4, MODULE6.P$4, MODULE7.P$4, MODULE8.P$4
USART2_TX: J1.22, J2.22, J3.22, J4.22, MODULE5.P$2, MODULE6.P$2, MODULE7.P$2, MODULE8.P$2

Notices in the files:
parts and their libraries:
SparkFun-Electromechanical: Licensing: CC v3.0 Share-Alike You are welcome to use this library for commercial purposes.
SparkFun-FreqCtrl: Licensing: Creative Commons ShareAlike 4.0 International - https://creativecommons.org/licenses/by-sa/4.0
